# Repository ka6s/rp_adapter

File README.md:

# rp_adapter : v4

# rp_adapter

This is the layout of the 4th iteration of this board.  Currently the design in this directory is the 
transceiver consisting of a connector to the Red Pitaya, the OpenHPSDR TAPR LPU, the OpenHPSDR TAPR T/R board, 
a 1W PA taken from the OpenHPSDR Penelope board, and a simple 18db ish LNA.  

The connecitivy is built to interface to an external amplifier, the Hermes RX Filter from EB104.ru and
the 300W LPF from EB104.ru. You need to get the amp keying from the EB104.ru LPF board. 

Enjoy

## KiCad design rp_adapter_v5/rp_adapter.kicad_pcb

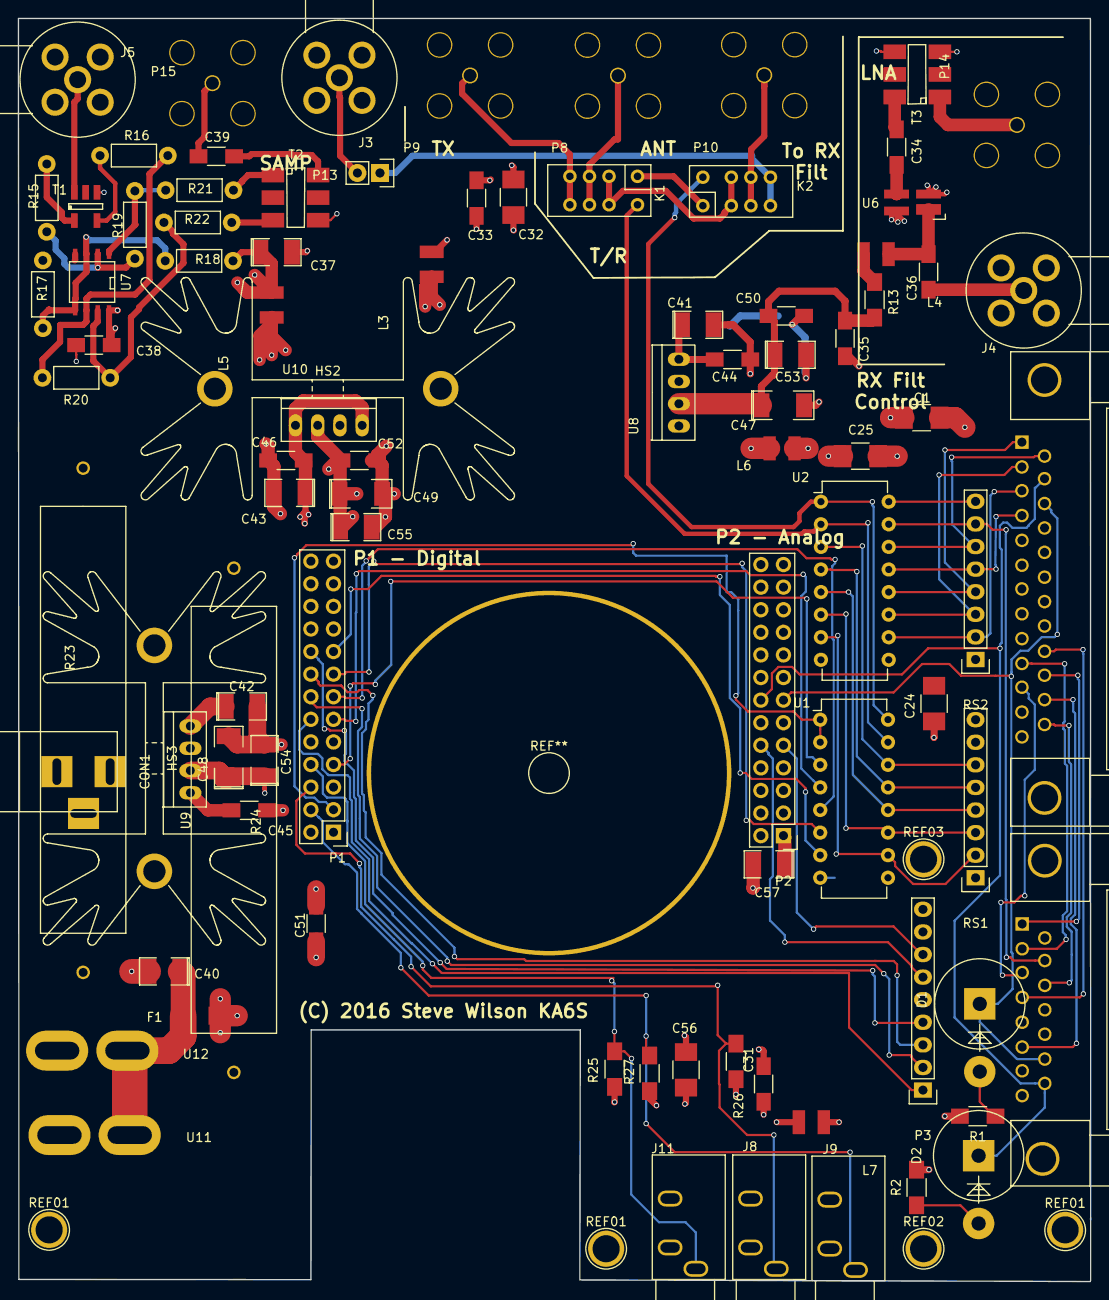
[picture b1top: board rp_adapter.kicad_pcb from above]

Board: 4 copper layers, 120.6 x 142.0 mm, 95 parts (0 on the bottom side), 80 nets.

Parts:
C1: 100uF; C_1210_HandSoldering
C24, C25, C32, C56: 1uF; C_1210_HandSoldering
C31, C33, C34, C35, C36, C38, C39, C44, C45, C46, C50, C51, C52: 0.1uF; C_1206_HandSoldering
C37, C41, C42, C43: 10uF; SMD-1210_Pol
C40, C53, C54, C55, C57: 100uF; SMD-1210_Pol
C47, C48, C49: 10uF; SMD-2010_Pol
CON1: BARREL_JACK
D1, D2: ZENER; Diode_P600_Vertical_AnodeUp
F1: FUSE; Fuse_SMD1206_HandSoldering
HS2, HS3: HEATSINK; Heatsink_Fischer_SK129-STS_42x25mm_2xDrill2.5mm
J1: DB15; DB15FC
J2: DB25; DB25FC
J3, J4, J5: SMA; SMA_F_RA
J8, J9, J11: JACK_2P; RA_3p5_audio_jack
K1, K2: RELAY_RF; RF_RELAY
L3, L4, L5, L6, L7: FB
P1, P2: CONN_02X13; Pin_Header_Straight_2x13
P3: CONN_01X09; Pin_Header_Straight_1x09
P8, P9, P10, P14, P15: BNC; BNC_VERTICAL
P13: CONN_01X02; Pin_Header_Straight_1x02
R1, R2: 1K; R_1206_HandSoldering
R13: 75; R_1206_HandSoldering
R15, R16: 100; Resistor_Horizontal_RM7mm
R17, R18, R19, R20: 1K; Resistor_Horizontal_RM7mm
R21, R22: 4R99; Resistor_Horizontal_RM7mm
R23, R24: 2R2; RES_10W
R25, R26, R27: 4.7K; R_1206_HandSoldering
REF01, REF01#2, REF01#3, REF02, REF03: 1pin
RS1, RS2: RSIP7; Pin_Header_Straight_1x08
T1: TC4-LT; TC4-1T
T2: ADT1.5-1
T3: ADT1-1; ADT1.5-1
U1, U2: ULN2004A; DIP-16_W7.62mm
U6: MAX2611; SOT-143_Handsoldering
U7: OPA26741C; SOIC-8-N
U8, U9: KA278R05; TO-220_4pin_vertical
U10: KA278R12; TO-220_4pin_vertical
U11, U12: PwrPole; RA_POWER_POLE

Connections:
+12V: C1.1, C24.1, C25.1, J1.5, L6.2, RS1.1, RS2.1, U1.9, U2.9
/extern_conn/3P3V_AUD: C31.1, C56.1, L7.1, R25.1, R26.1, R27.1
/extern_conn/ADCDAT: P1.14, P3.2
/extern_conn/BCLK: P1.12, P3.1
/extern_conn/DACDAT: P1.16, P3.3
/extern_conn/DASH: J8.1, P1.6, R26.2
/extern_conn/DOT: J11.1, P1.8, R25.2
/extern_conn/LRCLK: P1.18, P3.4
/extern_conn/PTT_IN: J9.1, P1.4, R27.2
/extern_conn/SCLK: P2.9, P3.7
/extern_conn/SDAT: P2.10, P3.6
/lna/5V_LNA: C35.1, C47.1, C50.1, C53.1, R13.1, U8.2
/lvlshift/12V_LVL_IN: C49.1, C52.1, C55.1, CON1.1, L3.2, L5.2, L6.1, U10.2
/lvlshift/ATTEN: P1.7, U1.3
/lvlshift/BA: RS1.5, U1.13, U2.4
/lvlshift/BATTN: RS1.6, U1.14, U2.3
/lvlshift/BB: RS1.4, U1.12, U2.5
/lvlshift/BC: RS1.3, U1.11, U2.6
/lvlshift/BD: RS1.2, U1.10, U2.7
/lvlshift/CATTN: J2.14, RS2.6, U2.14
/lvlshift/CBIAS: RS2.8, U2.16
/lvlshift/CONA: J2.4, RS2.5, U2.13
/lvlshift/CONB: J2.1, RS2.4, U2.12
/lvlshift/CONC: J2.2, RS2.3, U2.11
/lvlshift/COND: J2.3, RS2.2, U2.10
/lvlshift/CPTT: J1.10, RS2.7, U2.15
/lvlshift/OUTA: P1.11, U1.4
/lvlshift/OUTB: P1.13, U1.5
/lvlshift/OUTC: P1.15, U1.6
/lvlshift/OUTD: P1.17, U1.7
/lvlshift/PTT: P1.3, U1.1, U1.2
/lvlshift/PTT_OUT_RX: K2.8, U1.16, U2.1
/lvlshift/PTT_OUT_TX: K1.8, U1.15, U2.2
/lvlshift/lpf10: J1.11, J2.25
/lvlshift/lpf15: J1.6, J2.24
/lvlshift/lpf20: J1.3, J2.11
/lvlshift/lpf40: J1.1, J2.23
/lvlshift/lpf80: J1.2, J2.10
/lvlshift/lpf160: J1.4, J2.22
/mini_amp/AMP12V: C37.1, C38.1, L5.1, R18.1, U7.8
/ps/+13.8VA: C40.1, F1.1, U11.2, U12.2
/ps/+13.8VB: C43.1, C46.1, F1.2, R23.2, R24.2, U10.1, U10.4
/ps/+13.8VRA: C41.1, C44.1, R23.1, U8.1, U8.4
/ps/+13.8VRB: C42.1, C45.1, R24.1, U9.1, U9.4
/ps/RP_5V: C48.1, C51.1, C54.1, C57.1, P2.1, U9.2
/rp_conn/RP_3.3V: L7.2, P1.1, P1.2, P3.8
/rp_conn/SWR_F: D1.1, J1.14, J2.16, P2.13
/rp_conn/SWR_R: D2.1, J1.15, J2.15, P2.14
/tr_switch/12V_Relay: C32.1, C33.1, K1.1, K2.1, L3.1
Earth: J5.2, J5.3, J5.4, J5.5, T1.3
GND: C1.2, C24.2, C25.2, C31.2, C32.2, C33.2, C35.2, C37.2, C38.2, C40.2, C41.2, C42.2, C43.2, C44.2, C45.2, C46.2, C47.2, C48.2, C49.2, C50.2, C51.2, C52.2, C53.2, C54.2, C55.2, C56.2, C57.2, CON1.2, CON1.3, J1.7, J1.8, J1.9, J4.2, J4.3, J4.4, J4.5, J8.2, J8.3, J9.2, J9.3, J11.2, J11.3, P1.25, P1.26, P2.21, P2.22, P2.25, P2.26, P3.9, R1.2, R2.2, R17.2, T3.4, U1.8, U2.8, U6.2, U6.4, U7.4, U8.3, U9.3, U10.3, U11.1, U12.1
GNDA: J3.2, J3.3, J3.4, J3.5, P8.2, P9.2, P10.2
GNDPWR: P15.2, T2.4
GNDREF: P14.2, T3.3
unnamed: C34.1, T3.6
unnamed: C34.2, U6.3
unnamed: C36.1, L4.2, U6.1
unnamed: C36.2, J4.1
unnamed: C39.1, P15.1
unnamed: C39.2, T2.6
unnamed: D1.2, R1.1
unnamed: D2.2, R2.1
unnamed: J3.1, P13.2
unnamed: J5.1, T1.1
unnamed: K1.2, K1.7, K2.2, K2.7
unnamed: K1.3, K1.6, P8.1
unnamed: K1.4, K1.5, P9.1
unnamed: K2.3, K2.6, P10.1
unnamed: K2.4, K2.5, P13.1
unnamed: L4.1, R13.2
unnamed: P14.1, T3.1
unnamed: R15.1, R19.2, U7.2
unnamed: R15.2, T1.6
unnamed: R16.1, R20.2, U7.6
unnamed: R16.2, T1.4
unnamed: R17.1, R18.2, U7.3, U7.5
unnamed: R19.1, R21.1, U7.1
unnamed: R20.1, R22.2, U7.7
unnamed: R21.2, T2.1
unnamed: R22.1, T2.3

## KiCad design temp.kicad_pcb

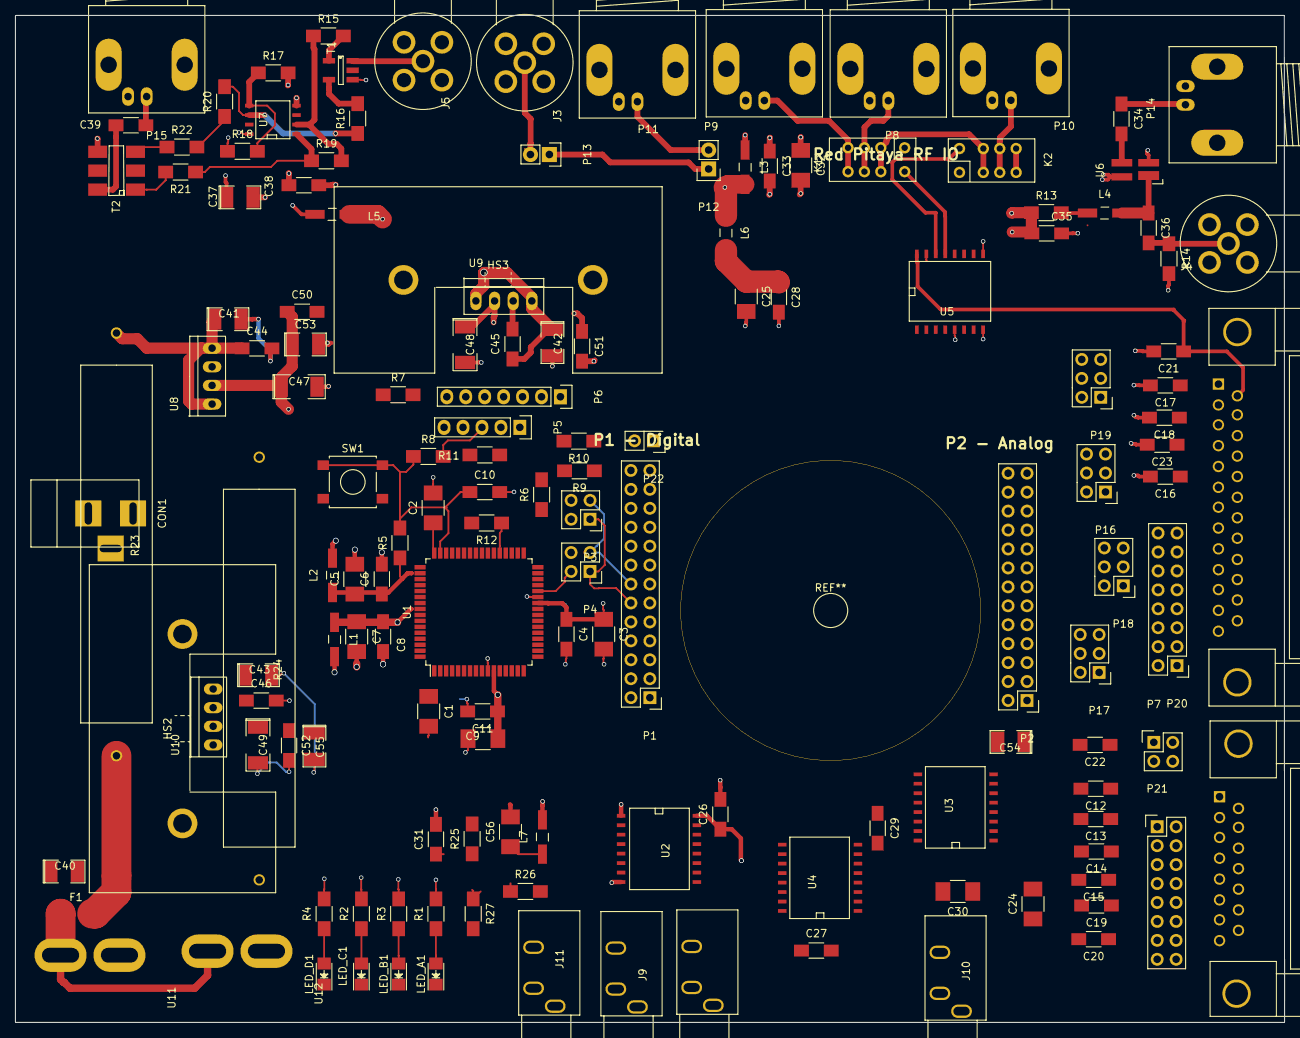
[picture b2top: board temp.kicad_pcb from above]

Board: 4 copper layers, 170.2 x 135.1 mm, 146 parts (0 on the bottom side), 122 nets.

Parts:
C1, C2, C3, C5, C7, C9, C24, C25, C32, C56: 1uF; C_1210_HandSoldering
C4, C6, C8, C10, C11, C26, C27, C28, C29, C31, C33, C34, C35, C36, C38, C39, C44, C45, C46, C50, C51, C52: 0.1uF; C_1206_HandSoldering
C12, C13, C14, C15, C16, C17, C18, C19, C20, C21, C22, C23: 100pF; C_1206_HandSoldering
C30: 10uF; C_1210_HandSoldering
C37, C41, C42, C43: 10uF; SMD-1210_Pol
C40, C53, C54, C55: 100uF; SMD-1210_Pol
C47, C48, C49: 10uF; SMD-2010_Pol
CON1: BARREL_JACK
F1: FUSE; Fuse_SMD1206_HandSoldering
HS2, HS3: HEATSINK; Heatsink-TO220
J1: DB15; DB15FC
J2: DB25; DB25FC
J3, J4, J5: SMA; SMA_F_RA
J8, J9, J10, J11: JACK_2P; RA_3p5_audio_jack
K1, K2: RELAY_RF; RF_RELAY
L1, L2: 0.47uH; Choke_SMD_1206_Handsoldering
L3, L4, L5, L6, L7: FB; Choke_SMD_1206_Handsoldering
LED_A1: LED; LED_1206
LED_B1: LED; LED_1206
LED_C1: LED; LED_1206
LED_D1: LED; LED_1206
P1, P2: CONN_02X13; Pin_Header_Straight_2x13
P3, P4, P7: CONN_02X02; Pin_Header_Straight_2x02
P5: CONN_01X05; Pin_Header_Straight_1x05
P6: CONN_01X07; Pin_Header_Straight_1x07
P8, P9, P10, P11, P14, P15: BNC; BNC_Socket_TYCO-AMP_LargePads
P12, P13: CONN_01X02; Pin_Header_Straight_1x02
P16, P17, P18, P19: CONN_02X03; Pin_Header_Straight_2x03
P20, P21: CONN_02X08; Pin_Header_Straight_2x08
P22: CONN_02X01; Pin_Header_Straight_2x01
R1, R2, R3, R4, R5, R25, R26, R27: 4.7K; R_1206_HandSoldering
R6, R7, R8, R9, R10, R11, R12: 0; R_1206_HandSoldering
R13: 75; R_1206_HandSoldering
R14: 50; R_1206_HandSoldering
R15, R16: 100; R_1206_HandSoldering
R17, R18, R19, R20: 1K; R_1206_HandSoldering
R21, R22: 4R99; R_1206_HandSoldering
R23, R24: 2R2; RES_10W
SW1: SW_PUSH; SW_SPST_B3S-1000
T1: TC4-LT; TC4-1T
T2: ADT1.5-1
U1: CY8C4247AXIM; LQFP-64_14x14mm_Pitch0.8mm
U2, U3, U4: 4504; SO-16-W
U5: ULN2003; SO-16-W
U6: MAX2611; SOT-143_Handsoldering
U7: OPA26741C; SOIC-8-N
U8, U9: KA278R05; TO-220_4pin_vertical
U10: KA278R12; TO-220_4pin_vertical
U11, U12: PwrPole; RA_POWER_POLE

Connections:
+12V: C24.1, C25.1, C26.1, C27.1, C28.1, C29.1, J1.5, L6.2, U2.16, U3.16, U4.16
/extern_conn/AUDIO_IN: C30.1, P16.5, P17.5, P18.5, P19.5
/extern_conn/DASH: J8.1, P1.6, R26.2
/extern_conn/DOT: J11.1, P1.8, R25.2
/extern_conn/PTT_IN: J9.1, P1.4, R27.2
/filt_if/I2C_CLOCK: P1.14, P3.3, P4.3
/filt_if/I2C_DATA: P1.12, P3.1, P4.1
/filt_if/I2C_SCL: P6.3, R6.2
/filt_if/I2C_SDA: P6.5, R11.2
/filt_if/LPF0: U1.2, U2.14
/filt_if/LPF1: U1.3, U3.14
/filt_if/LPF2: U1.4, U2.5
/filt_if/LPF3: U1.5, U3.5
/filt_if/LPF4: U1.6, U2.3
/filt_if/LPF5: U1.7, U3.3
/filt_if/LPF6: U1.8, U4.3
/filt_if/LPF7: U1.9, U4.5
/filt_if/OUTA: LED_A1.1, U1.39, U2.9
/filt_if/OUTB: LED_B1.1, U1.40, U3.9
/filt_if/OUTC: LED_C1.1, U1.41, U2.11
/filt_if/OUTD: LED_D1.1, U1.42, U3.11
/filt_if/P4_VDDA: C7.1, C8.1, C9.1, C11.1, L1.1, U1.11, U1.56
/filt_if/P4_VDDD: C5.1, C6.1, L2.1, R5.1, U1.50
/filt_if/RESET: P5.3, R8.2
/filt_if/SAR_BYPASS: C1.1, U1.1
/filt_if/SWD_CLK: P5.4, R9.2
/filt_if/SWD_DATA: P5.5, R10.2
/filt_if/UART_RX: P6.6, R7.2
/filt_if/UART_TX: P6.7, R12.2
/filt_if/VCCD: C2.1, U1.48
/filt_if/XRES: C10.1, R5.2, R8.1, SW1.1, U1.47
/lna/5V_LNA: C35.1, C47.1, C50.1, C53.1, R13.1, U8.2
/lvlshift/12V_LVL_IN: C49.1, C52.1, C55.1, CON1.1, L3.2, L5.2, L6.1, U10.2
/lvlshift/ATTEN: P1.5, U2.7
/lvlshift/PTT: P1.3, U3.7
/lvlshift/PTT_OUT_RX: K2.8, U5.14
/lvlshift/PTT_OUT_TX: K1.8, U5.13
/lvlshift/SWR_F: P16.1, P17.1, P18.1, P19.1, P21.13
/lvlshift/lpf10o: J2.25, P20.1
/lvlshift/lpf15o: J2.24, P20.3
/lvlshift/lpf20o: J2.11, P20.5
/lvlshift/lpf40o: J2.23, P20.7
/lvlshift/lpf80o: J2.10, P20.9
/lvlshift/lpf160o: J2.22, P20.11
/lvlshift/lpf_0_12v: C12.1, P21.1, U2.15
/lvlshift/lpf_1_12V: C13.1, P21.3, U3.15
/lvlshift/lpf_2_12v: C14.1, P21.5, U2.4
/lvlshift/lpf_3_12v: C15.1, P21.7, U3.4
/lvlshift/lpf_4_12v: C19.1, P21.9, U2.2
/lvlshift/lpf_5_12v: C20.1, P21.11, U3.2
/lvlshift/lpf_10: J1.11, P20.2, P21.2
/lvlshift/lpf_15: J1.6, P20.4, P21.4
/lvlshift/lpf_20: J1.3, P20.6, P21.6
/lvlshift/lpf_40: J1.1, P20.8, P21.8
/lvlshift/lpf_80: J1.2, P20.10, P21.10
/lvlshift/lpf_160: J1.4, P20.12, P21.12
/lvlshift/swr_fd: J1.14, P20.14, P21.14
/lvlshift/swr_rv: J1.15, P20.16, P21.16
/lvlshift/swrf: J2.16, P20.13
/lvlshift/swrr: J2.15, P20.15
/mini_amp/AMP12V: C37.1, C38.1, L5.1, R18.1, U7.8
/ps/+13.8VA: C40.1, F1.1, U11.2, U12.2
/ps/+13.8VB: C43.1, C46.1, F1.2, R23.2, R24.2, U10.1, U10.4
/ps/+13.8VRA: C41.1, C44.1, R23.1, U8.1, U8.4
/ps/+13.8VRB: C42.1, C45.1, R24.1, U9.1, U9.4
/ps/RP_5V: C48.1, C51.1, C54.1, P2.1, U9.2
/rp_conn/SWR_R: P16.3, P17.3, P18.3, P19.3
/tr_switch/12V_Relay: C32.1, C33.1, K1.1, K2.1, L3.1
GND: C1.2, C2.2, C3.2, C4.2, C5.2, C6.2, C7.2, C8.2, C9.2, C10.2, C11.2, C12.2, C13.2, C14.2, C15.2, C16.2, C17.2, C18.2, C19.2, C20.2, C21.2, C22.2, C23.2, C24.2, C25.2, C26.2, C27.2, C28.2, C29.2, C31.2, C32.2, C33.2, C35.2, C37.2, C38.2, C40.2, C41.2, C42.2, C43.2, C44.2, C45.2, C46.2, C47.2, C48.2, C49.2, C50.2, C51.2, C52.2, C53.2, C54.2, C55.2, C56.2, CON1.2, CON1.3, J1.7, J1.8, J1.9, J3.2, J3.3, J3.4, J3.5, J4.2, J4.3, J4.4, J4.5, J5.2, J5.3, J5.4, J5.5, J8.2, J8.3, J9.2, J9.3, J10.2, J10.3, J11.2, J11.3, P1.25, P1.26, P2.21, P2.22, P2.25, P2.26, P5.2, P8.2, P9.2, P10.2, P11.2, P14.2, P15.2, R14.2, R17.2, SW1.2, T1.3, T2.4, U1.10, U1.17, U1.49, U1.57, U2.8, U3.8, U4.8, U5.5, U5.6, U5.7, U5.8, U5.9, U6.2, U6.4, U7.4, U8.3, U9.3, U10.3, U11.1, U12.1
unnamed: C16.1, J2.4, U2.10
unnamed: C17.1, J2.1, U3.10
unnamed: C18.1, J2.2, U2.12
unnamed: C21.1, J2.14, U5.16
unnamed: C22.1, P7.1, U5.15
unnamed: C23.1, J2.3, U3.12
unnamed: C30.2, J10.1
unnamed: C31.1, C56.1, L7.1, R25.1, R26.1, R27.1
unnamed: C34.1, P14.1
unnamed: C34.2, U6.3
unnamed: C36.1, L4.2, U6.1
unnamed: C36.2, J4.1, R14.1
unnamed: C39.1, P15.1
unnamed: C39.2, T2.6
unnamed: J1.10, P7.2, P7.4
unnamed: J3.1, P13.2
unnamed: J5.1, T1.1
unnamed: K1.2, K1.7, K2.2, K2.7
unnamed: K1.3, K1.6, P8.1
unnamed: K1.4, K1.5, P9.1
unnamed: K2.3, K2.6, P10.1
unnamed: K2.4, K2.5, P12.1, P13.1
unnamed: L4.1, R13.2
unnamed: LED_A1.2, R1.1
unnamed: LED_B1.2, R3.1
unnamed: LED_C1.2, R2.1
unnamed: LED_D1.2, R4.1
unnamed: P3.2, U1.52
unnamed: P3.4, U1.51
unnamed: P4.2, R11.1, U1.28
unnamed: P4.4, R6.1, U1.27
unnamed: P7.3, U3.6, U5.2, U5.3, U5.4
unnamed: P11.1, P12.2
unnamed: P2.13, P16.2, P16.4, P16.6
unnamed: P2.15, P17.2, P17.4, P17.6
unnamed: P2.16, P18.2, P18.4, P18.6
unnamed: P2.14, P19.2, P19.4, P19.6
unnamed: P5.1, P22.1
unnamed: R7.1, U1.38
unnamed: R9.1, U1.21
unnamed: R10.1, U1.20
unnamed: R12.1, U1.37
unnamed: R15.1, R19.2, U7.2
unnamed: R15.2, T1.6
unnamed: R16.1, R20.2, U7.6
unnamed: R16.2, T1.4
unnamed: R17.1, R18.2, U7.3, U7.5
unnamed: R19.1, R21.1, U7.1
unnamed: R20.1, R22.2, U7.7
unnamed: R21.2, T2.1
unnamed: R22.1, T2.3
unnamed: U2.6, U5.1
VCC: C3.1, C4.1, L1.2, L2.2, L7.2, P1.1, P1.2, P22.2, R1.2, R2.2, R3.2, R4.2, U1.26, U2.1, U2.13, U3.1, U3.13, U4.1, U4.13

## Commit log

2016-10-28 Add License and update README.md
2017-12-02 Add pictures for use in Wiki
2017-12-02 Add BlockDiag.jpg
2017-12-02 Add LevelShifter image
2017-12-02 Add One Watt PA picture
2017-12-02 Add DebugRev1 jpg
2017-12-02 Add Power Add On Jpg
2017-12-02 Upload Mezzanine Power Jpg

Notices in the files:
rp_adapter_v5/rp_adapter.kicad_pcb:
(C) 2016 Steve Wilson KA6S
